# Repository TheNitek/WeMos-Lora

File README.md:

Note: This is a fork from https://github.com/hallard/WeMos-Lora reducing complexity (no display connector, no LEDs, no button) and freeing GPIO16/D0 to allow deep sleep

ESP8266 WeMos Shield for HopeRF RFM95 RFM96 RFM98 Lora Modules
==============================================================

This shield is used to hold HopeRF [Lora module][4] Software with WeMos ESP8266 boards it has just few minimal features. 
- Placement for RFM95/96/98 Lora module
- Placement for choosing single Wire, SMA or u-FL Antenna type 

You can find more information on WeMos on their [site][1], it's really well documented.
I now use WeMos boards instead of NodeMCU's one because they're just smaller, features remains the same, but I also suspect WeMos regulator far better quality than the one used on NodeMCU that are just fake of originals AMS117 3V3.

Boards arrived from OSHPark, I tested them, works fine with forked version of [single Channel LoRaWAN Gateway][5] but you can use any program that is compatible with RFM95 Lora module according it to real pinout.

Detailed Description
====================

Look at the schematics for more informations.

SPI connexion is classic (MOSI/MISO/CLK), Chip Select is connected with GPIO2.

Other pins that may need be adapted into code (for example if you use TTN network gateway code) according to the following pinout

Please not that to avoid 3 GPIOs for DIO0,DIO1,DIO2 Interrupt, these 3 are OR'ed with 3 diodes, respectively named D2,D3 and D4. This permit to use only one IRQ pin (here GPIO15). This is only possible because on IRQ routine the RFM9x IRQ register is read and then software knows which one has been triggered.
You can see more details ont this dedicated LMIC [Pull Request][6]

```
   WeMos D1          RFM9x Module
  GPIO12 (D6) <----> MISO
  GPIO13 (D7) <----> MOSI
  GPIO14 (D5) <----> CLK
  GPIO15 (D8) <----> DIO0/D2 OR DIO1/D3 OR DIO2/D4
  GPIO02 (D4) <----> SEL (Chip Select)
  RST         <----> RST
```

### Schematic  

### Boards  

You can order the PCB of this board at [PCBs.io][3] if you do so, PCBs.io give me little discount that allow me to buy some new created boards.

### Assembled boards

### License

http://unlicense.org/

[1]: http://www.wemos.cc/wiki/doku.php?id=en:d1_mini
[3]: https://pcbs.io/share/4XG02
[4]: http://www.hoperf.com/rf_transceiver/lora/
[5]: https://github.com/hallard/ESP-1ch-Gateway/
[6]: https://github.com/matthijskooijman/arduino-lmic/pull/34

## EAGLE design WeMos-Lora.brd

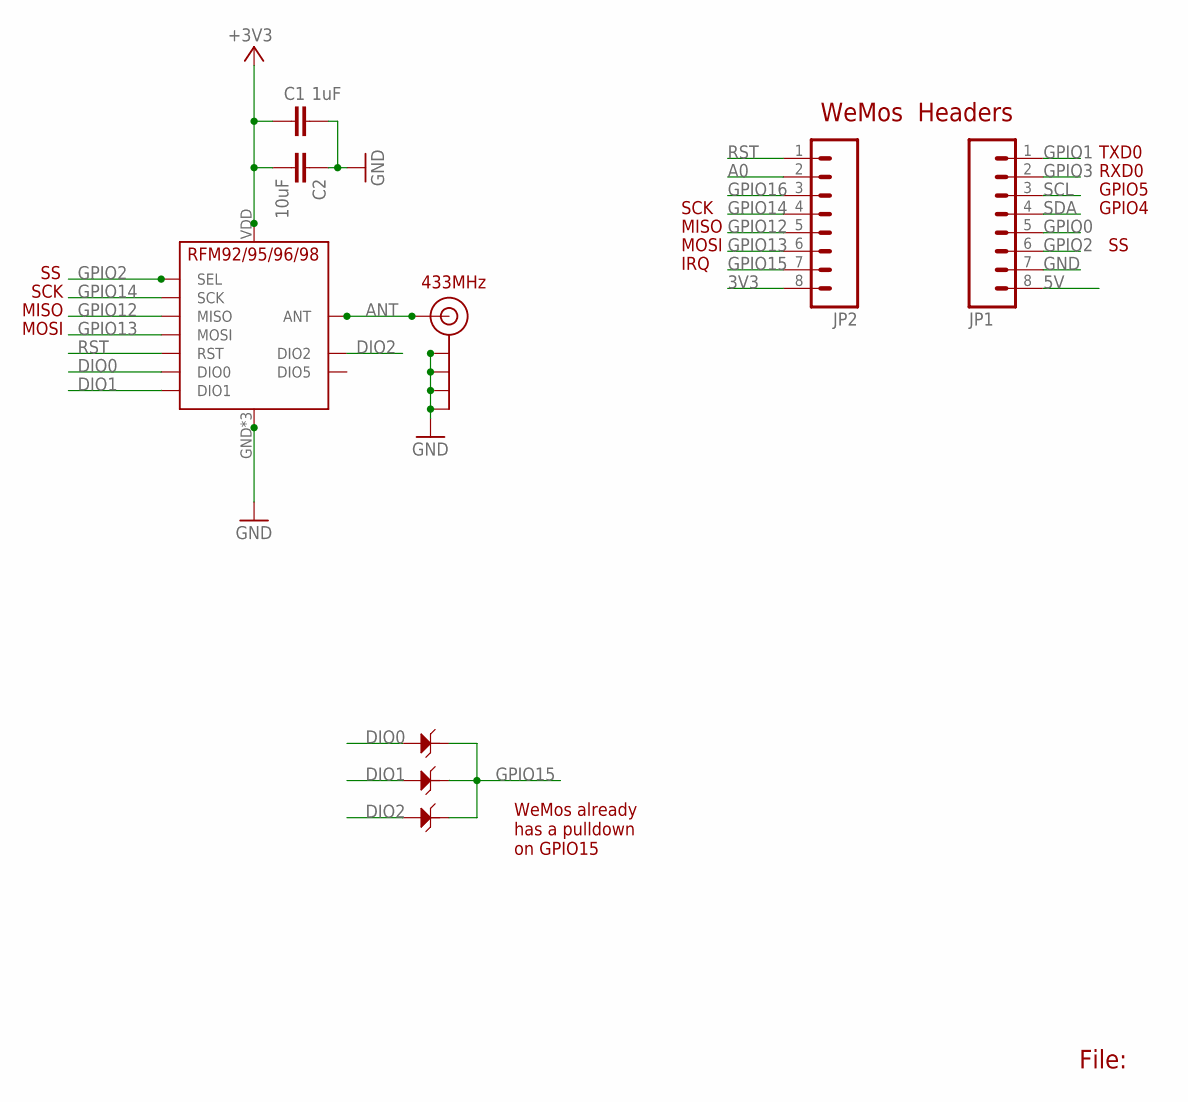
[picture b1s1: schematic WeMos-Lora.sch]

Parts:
C1: 1uF; 0805-CAP-LARGEPADS
C2: 10uF; 0805-CAP-LARGEPADS
D2, D3, D4: 1N4148; SOD123-2.7X1.6
J$2: ANTENNATINY; SMA_UFL_PAD_TINY
JP1, JP2: M08NO_SILK_FEMALE_PTH; 1X08_NO_SILK
U$5: RFM95

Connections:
3V3: C1.2, C2.2, JP2.8, U$5.VDD (VCC)
5V: JP1.8
A0: JP2.2
ANT: J$2.ANT1 (SIGNAL), J$2.ANT2 (SIGNAL), J$2.ANT3 (SIGNAL), U$5.ANT
DIO0: D2.1, U$5.DIO0
DIO1: D3.1, U$5.DIO1
DIO2: D4.1, U$5.DIO2
GND: C1.1, C2.1, J$2.GND1 (GND), J$2.GND2 (GND), J$2.GND3 (GND), J$2.GND4 (GND), JP1.7, U$5.GND, U$5.GND1 (GND), U$5.GND2 (GND)
GPIO0: JP1.5
GPIO1: JP1.1
GPIO2: JP1.6, U$5.NSS (SEL)
GPIO3: JP1.2
GPIO12: JP2.5, U$5.MISO
GPIO13: JP2.6, U$5.MOSI
GPIO14: JP2.4, U$5.SCK
GPIO15: D2.2, D3.2, D4.2, JP2.7
GPIO16: JP2.3
RST: JP2.1, U$5.RST
SCL: JP1.3
SDA: JP1.4

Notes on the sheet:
File:
MISO
GPIO4
GPIO5
RXD0
TXD0
MOSI
SCK
IRQ
WeMos Headers
433MHz
WeMos already has a pulldown on GPIO15

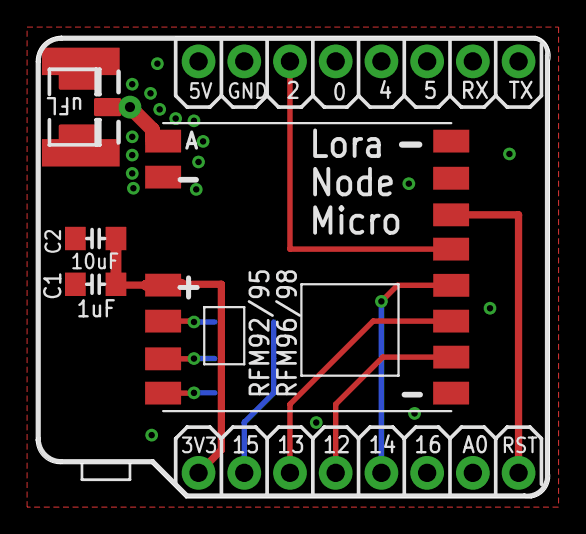
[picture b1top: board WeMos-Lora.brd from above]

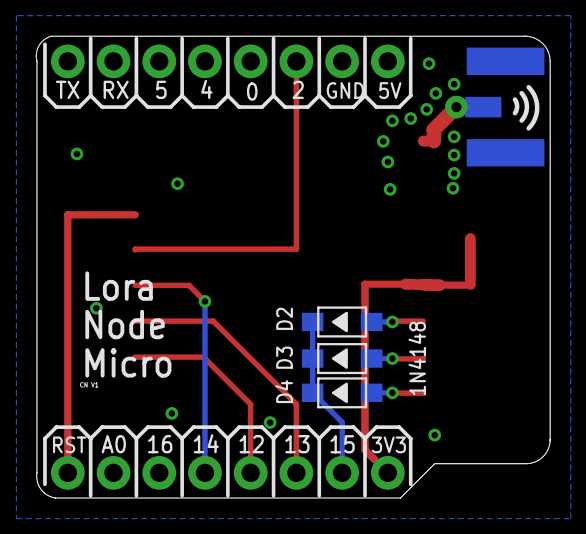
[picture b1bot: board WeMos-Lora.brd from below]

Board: 2 copper layers, 28.6 x 25.7 mm, 9 parts (3 on the bottom side), 12 nets.

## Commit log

2017-04-05 * Removed LEDs + Switch * Freed GPIO16
2017-04-05 Removed display connector
2017-04-06 Fixed misplaced label
2017-04-07 Remove useless routes
2017-04-26 update pictures and images
2017-04-26 fix images
2017-04-26 Update readme.md
    Updated pictures and changed text to match Lora Node Micro
2017-04-27 Update readme.md again
    Fix formating

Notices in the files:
parts and their libraries:
SparkFun-Connectors: Licensing: Creative Commons ShareAlike 4.0 International - https://creativecommons.org/licenses/by-sa/4.0
